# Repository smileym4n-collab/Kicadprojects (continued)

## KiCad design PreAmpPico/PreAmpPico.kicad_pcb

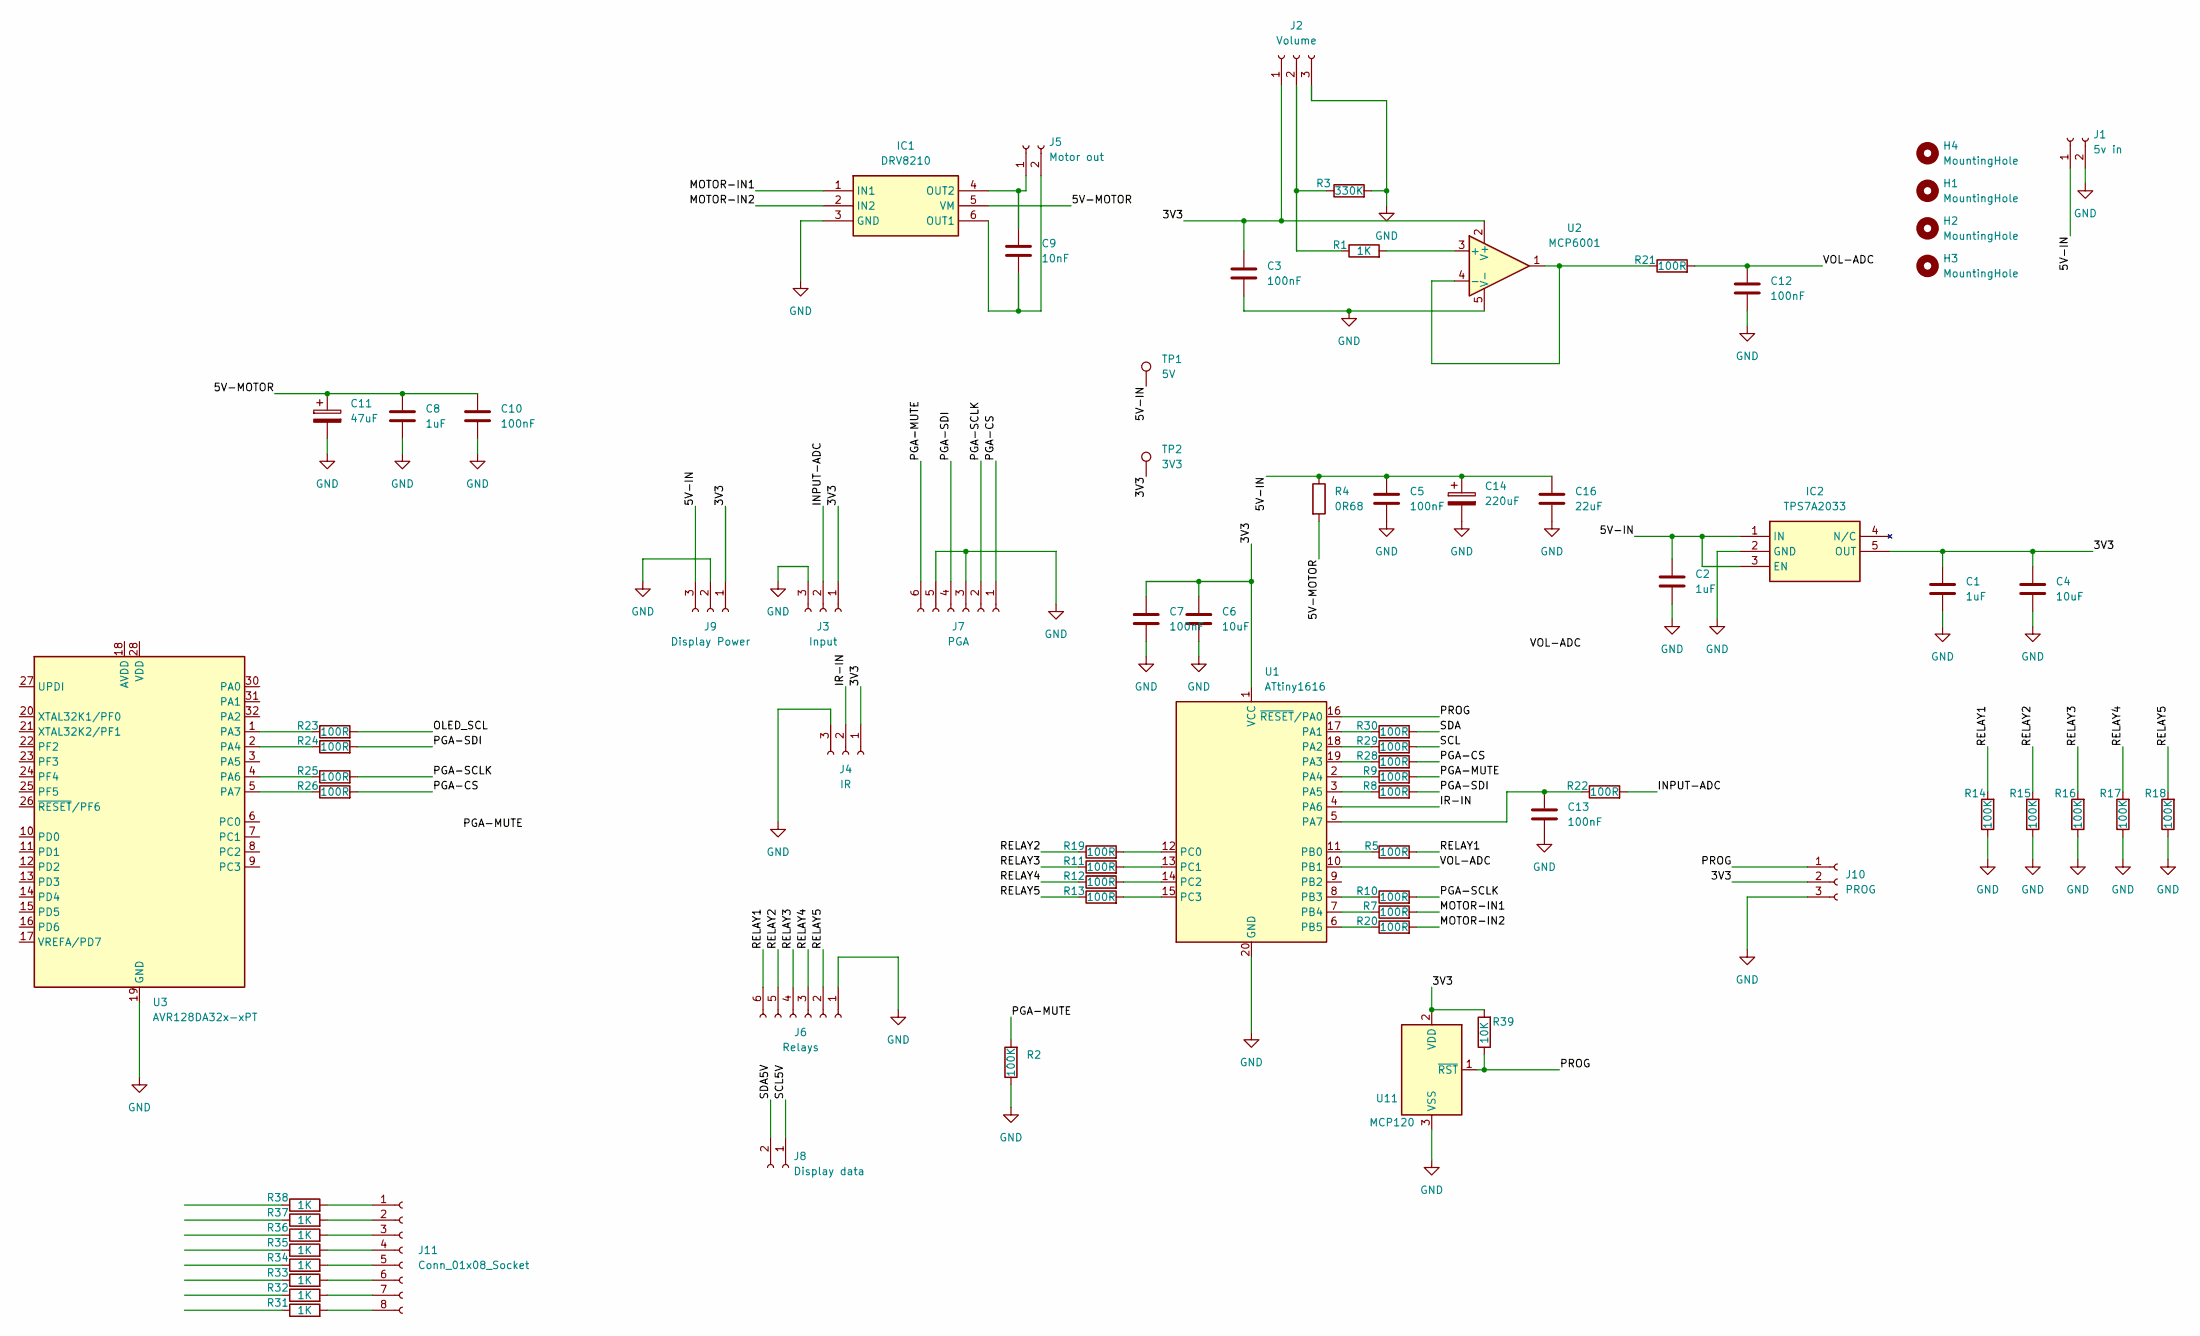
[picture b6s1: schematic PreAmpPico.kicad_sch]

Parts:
C1, C2, C8: 1uF; C_1206_3216Metric_Pad1.33x1.80mm_HandSolder
C3, C5, C7, C10, C12, C13: 100nF; C_1206_3216Metric_Pad1.33x1.80mm_HandSolder
C4, C6: 10uF; C_1206_3216Metric_Pad1.33x1.80mm_HandSolder
C9: 10nF; C_0805_2012Metric_Pad1.18x1.45mm_HandSolder
C11: 47uF; CP_Radial_D6.3mm_P2.50mm
C14: 220uF; CP_Radial_D6.3mm_P2.50mm
C16: 22uF; C_1206_3216Metric_Pad1.33x1.80mm_HandSolder
H1, H2, H3, H4: MountingHole; MountingHole_4mm
IC1: DRV8210; Mouser Part Number 595-DRV8210DRLR
IC2: TPS7A2033; SOT95P280X145-5N; Mouser Part Number 595-TPS7A2033PDBVR
J1: 5v in; JST_XH_B2B-XH-A_1x02_P2.50mm_Vertical
J2: Volume; JST_XH_B3B-XH-A_1x03_P2.50mm_Vertical
J3: Input; JST_XH_B3B-XH-A_1x03_P2.50mm_Vertical
J4: IR; JST_XH_B3B-XH-A_1x03_P2.50mm_Vertical
J5: Motor out; JST_XA_B02B-XASK-1_1x02_P2.50mm_Vertical
J6: Relays; JST_XH_B6B-XH-A_1x06_P2.50mm_Vertical
J7: PGA; JST_XH_B6B-XH-A_1x06_P2.50mm_Vertical
J8: Display data; JST_XA_B02B-XASK-1_1x02_P2.50mm_Vertical
J9: Display Power; JST_XH_B3B-XH-A_1x03_P2.50mm_Vertical
J10: PROG; PinSocket_1x03_P2.54mm_Vertical
J11: Conn_01x08_Socket; PinHeader_1x08_P2.54mm_Vertical
R1, R31, R32, R33, R34, R35, R36, R37, R38: 1K; R_0805_2012Metric_Pad1.20x1.40mm_HandSolder
R2, R14, R15, R16, R17, R18: 100K; R_0805_2012Metric_Pad1.20x1.40mm_HandSolder
R3: 330K; R_0805_2012Metric_Pad1.20x1.40mm_HandSolder
R4: 0R68; R_1206_3216Metric_Pad1.30x1.75mm_HandSolder
R5, R7, R8, R9, R10, R11, R12, R13, R19, R20, R21, R22, R23, R24, R25, R26, R28, R29, R30: 100R; R_0805_2012Metric_Pad1.20x1.40mm_HandSolder
R39: 10K; R_0805_2012Metric_Pad1.20x1.40mm_HandSolder
TP1: 5V; TestPoint_Pad_2.0x2.0mm
TP2: 3V3; TestPoint_Pad_2.0x2.0mm
U1: ATtiny1616; SSOP-20_5.3x7.2mm_P0.65mm
U2: MCP6001; SOT-23-5
U3: AVR128DA32x-xPT; TQFP-32_7x7mm_P0.8mm
U11: MCP120; SOT-23

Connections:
/3V3: C1.1, C3.1, C4.1, C6.1, C7.1, IC2.5 (OUT), J2.1, J3.1, J4.1, J9.1, J10.2, R39.2, TP2.1 (1_1), U1.1 (VCC), U2.2 (V+), U11.2 (VDD)
/5V-IN: C2.1, C5.1, C14.1, C16.1, IC2.1 (IN), IC2.3 (EN), J1.1, J9.3, R4.1, TP1.1 (1_1)
/5V-MOTOR: C8.1, C10.1, C11.1, IC1.5 (VM), R4.2
/INPUT-ADC: J3.2, R22.2
/IR-IN: J4.2, U1.4 (PA6)
/MOTOR-IN1: IC1.1 (IN1), R7.2
/MOTOR-IN2: IC1.2 (IN2), R20.2
/PGA-CS: J7.1, R26.2, R28.2
/PGA-MUTE: J7.6, R2.2, R9.2
/PGA-SCLK: J7.2, R10.2, R25.2
/PGA-SDI: J7.4, R8.2, R24.2
/PROG: J10.1, R39.1, U1.16 (~RESET/PA0), U11.1 (~RST)
/RELAY1: J6.6, R5.2, R14.2
/RELAY2: J6.5, R15.2, R19.1
/RELAY3: J6.4, R11.1, R16.2
/RELAY4: J6.3, R12.1, R17.2
/RELAY5: J6.2, R13.1, R18.2
/SCL: R29.2
/SCL5V: J8.1
/SDA: R30.2
/SDA5V: J8.2
/VOL-ADC: C12.1, R21.2, U1.10 (PB1)
unnamed: C9.2, IC1.6 (OUT1), J5.2
unnamed: C9.1, IC1.4 (OUT2), J5.1
unnamed: J2.2, R1.1, R3.1
unnamed: J11.1, R38.2
unnamed: J11.2, R37.2
unnamed: J11.3, R36.2
unnamed: J11.4, R35.2
unnamed: J11.5, R34.2
unnamed: J11.6, R33.2
unnamed: J11.7, R32.2
unnamed: J11.8, R31.2
unnamed: R23.1, U3.1 (PA3)
unnamed: R24.1, U3.2 (PA4)
unnamed: R25.1, U3.4 (PA6)
unnamed: R26.1, U3.5 (PA7)
unnamed: R30.1, U1.17 (PA1)
unnamed: R29.1, U1.18 (PA2)
unnamed: R28.1, U1.19 (PA3)
unnamed: R9.1, U1.2 (PA4)
unnamed: R8.1, U1.3 (PA5)
unnamed: C13.1, R22.1, U1.5 (PA7)
unnamed: R5.1, U1.11 (PB0)
unnamed: R10.1, U1.8 (PB3)
unnamed: R7.1, U1.7 (PB4)
unnamed: R20.1, U1.6 (PB5)
unnamed: R19.2, U1.12 (PC0)
unnamed: R11.2, U1.13 (PC1)
unnamed: R12.2, U1.14 (PC2)
unnamed: R13.2, U1.15 (PC3)
unnamed: R1.2, U2.3 (+)
unnamed: R21.1, U2.1, U2.4 (-)

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
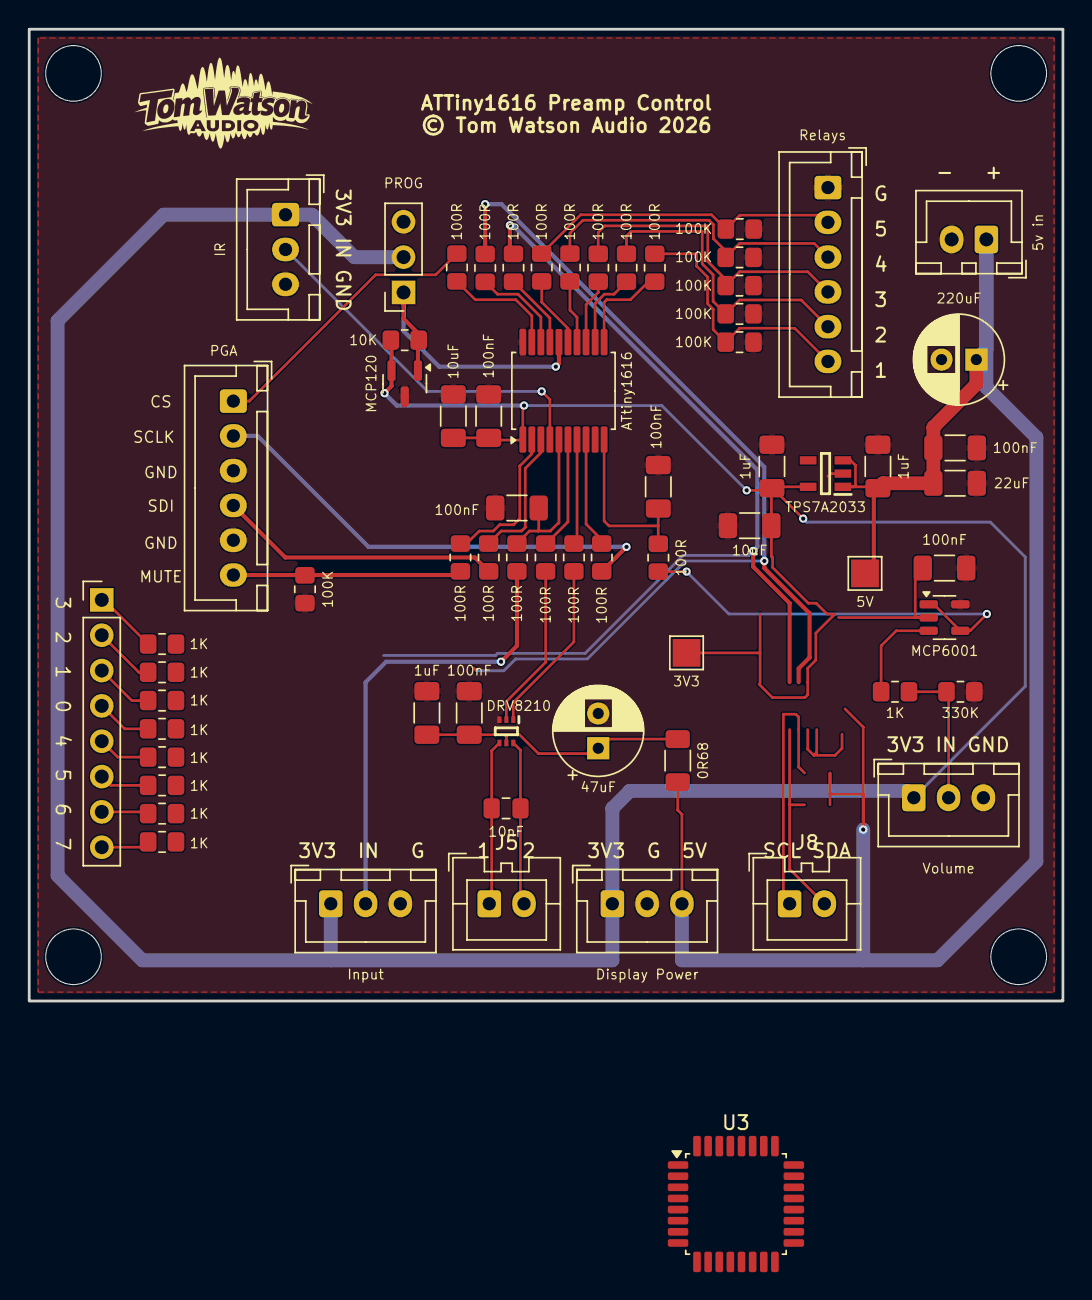
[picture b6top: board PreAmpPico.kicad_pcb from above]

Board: 2 copper layers, 74.3 x 69.9 mm, 71 parts (0 on the bottom side), 47 nets.

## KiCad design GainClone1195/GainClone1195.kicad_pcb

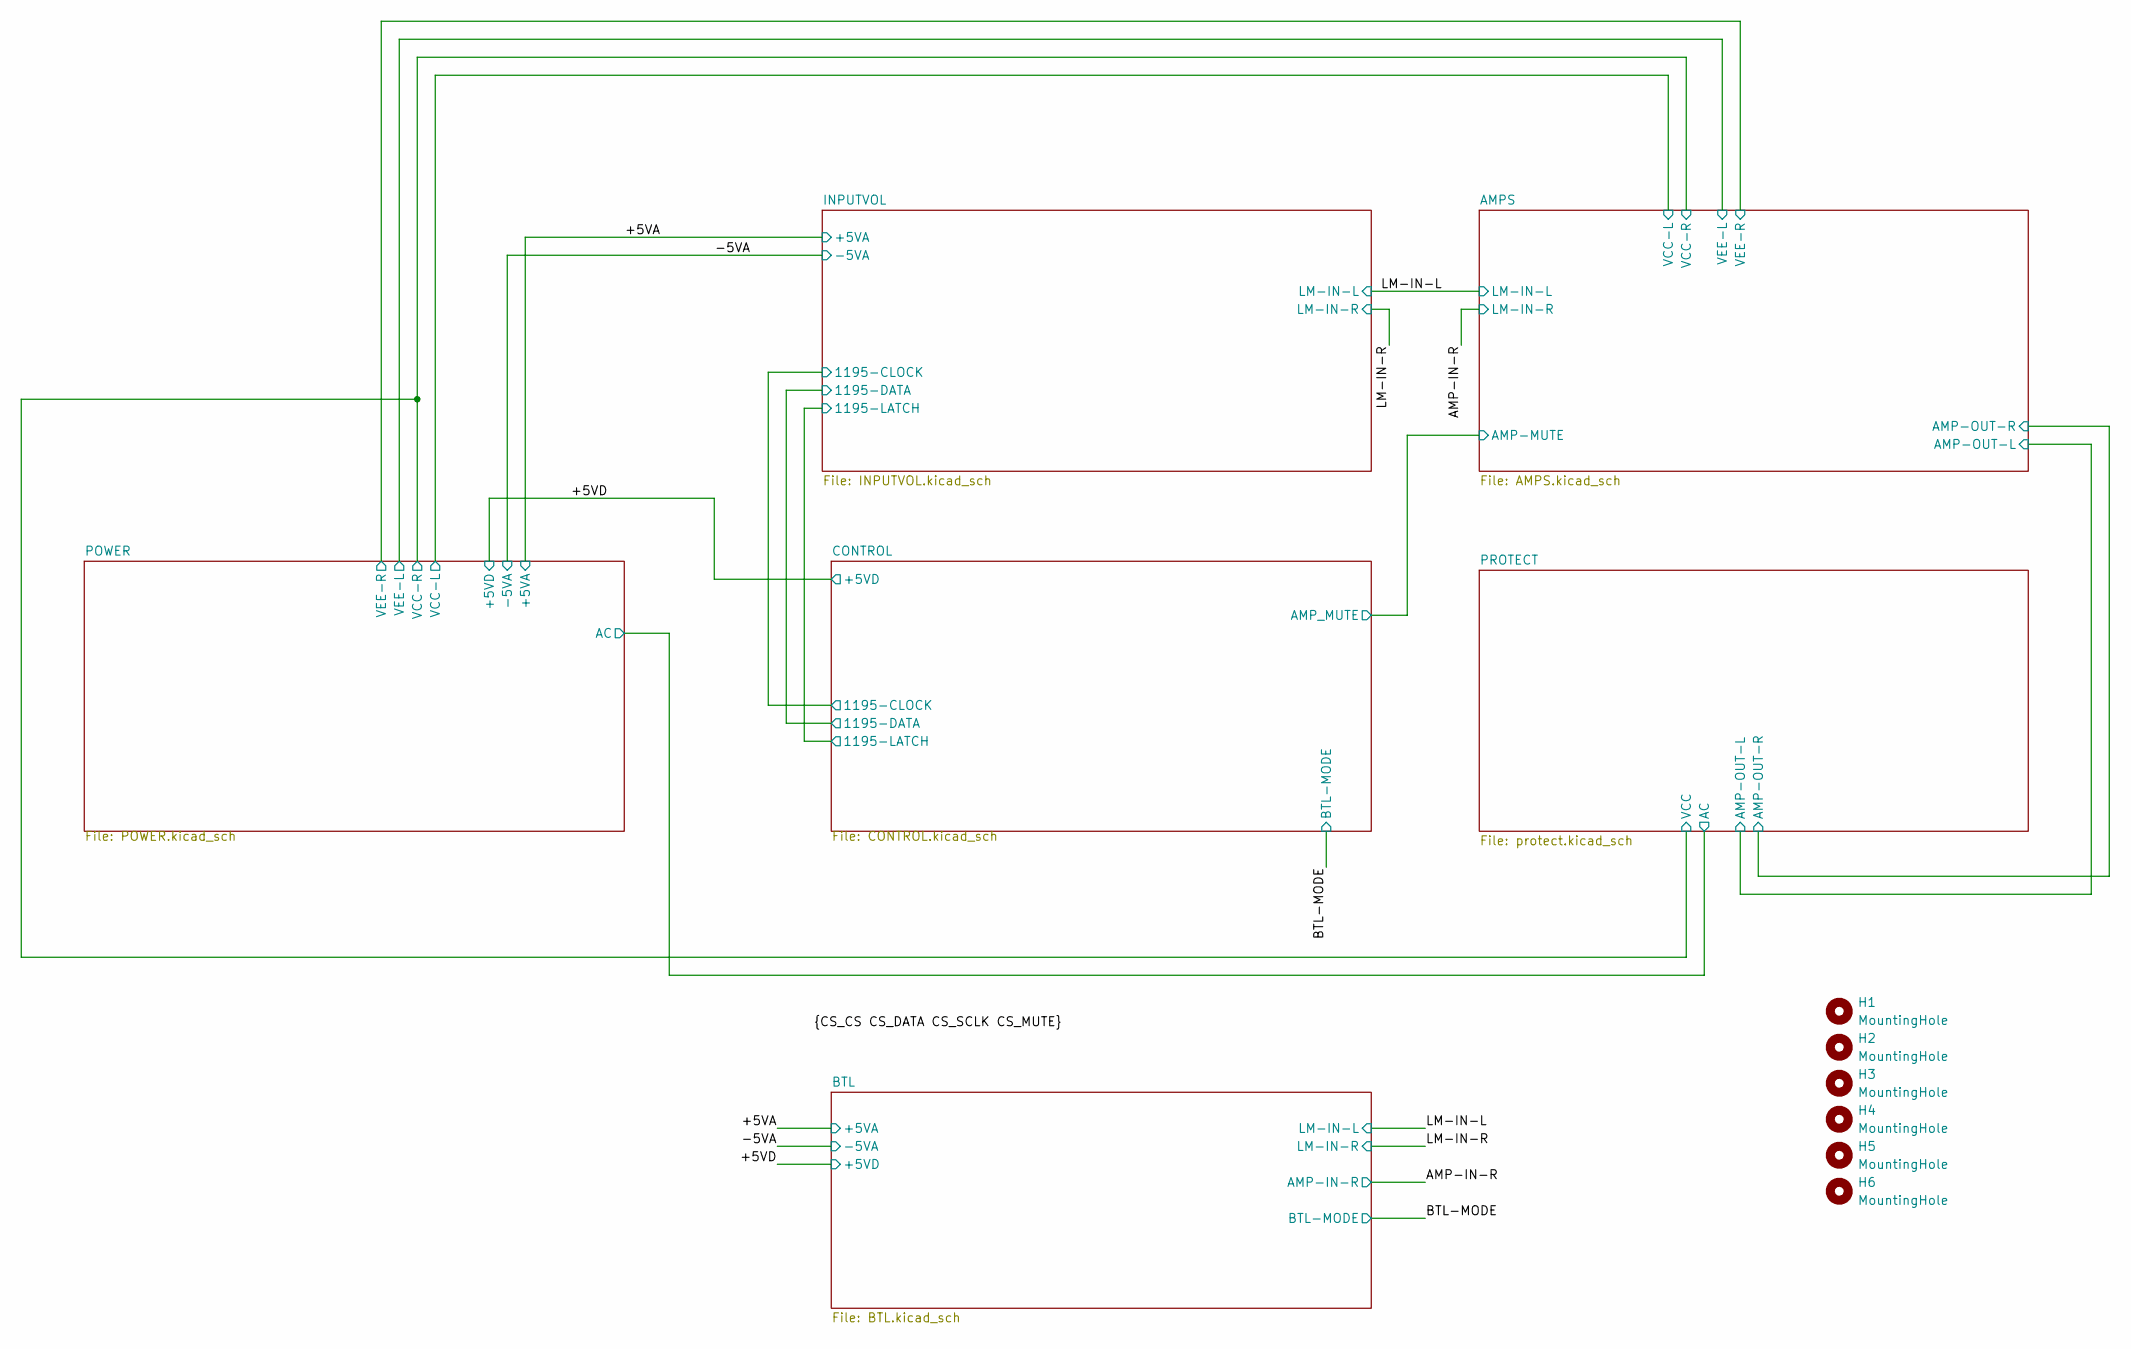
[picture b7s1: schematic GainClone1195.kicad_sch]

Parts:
H1, H2, H3, H4, H5, H6: MountingHole; MountingHole_3.2mm_M3

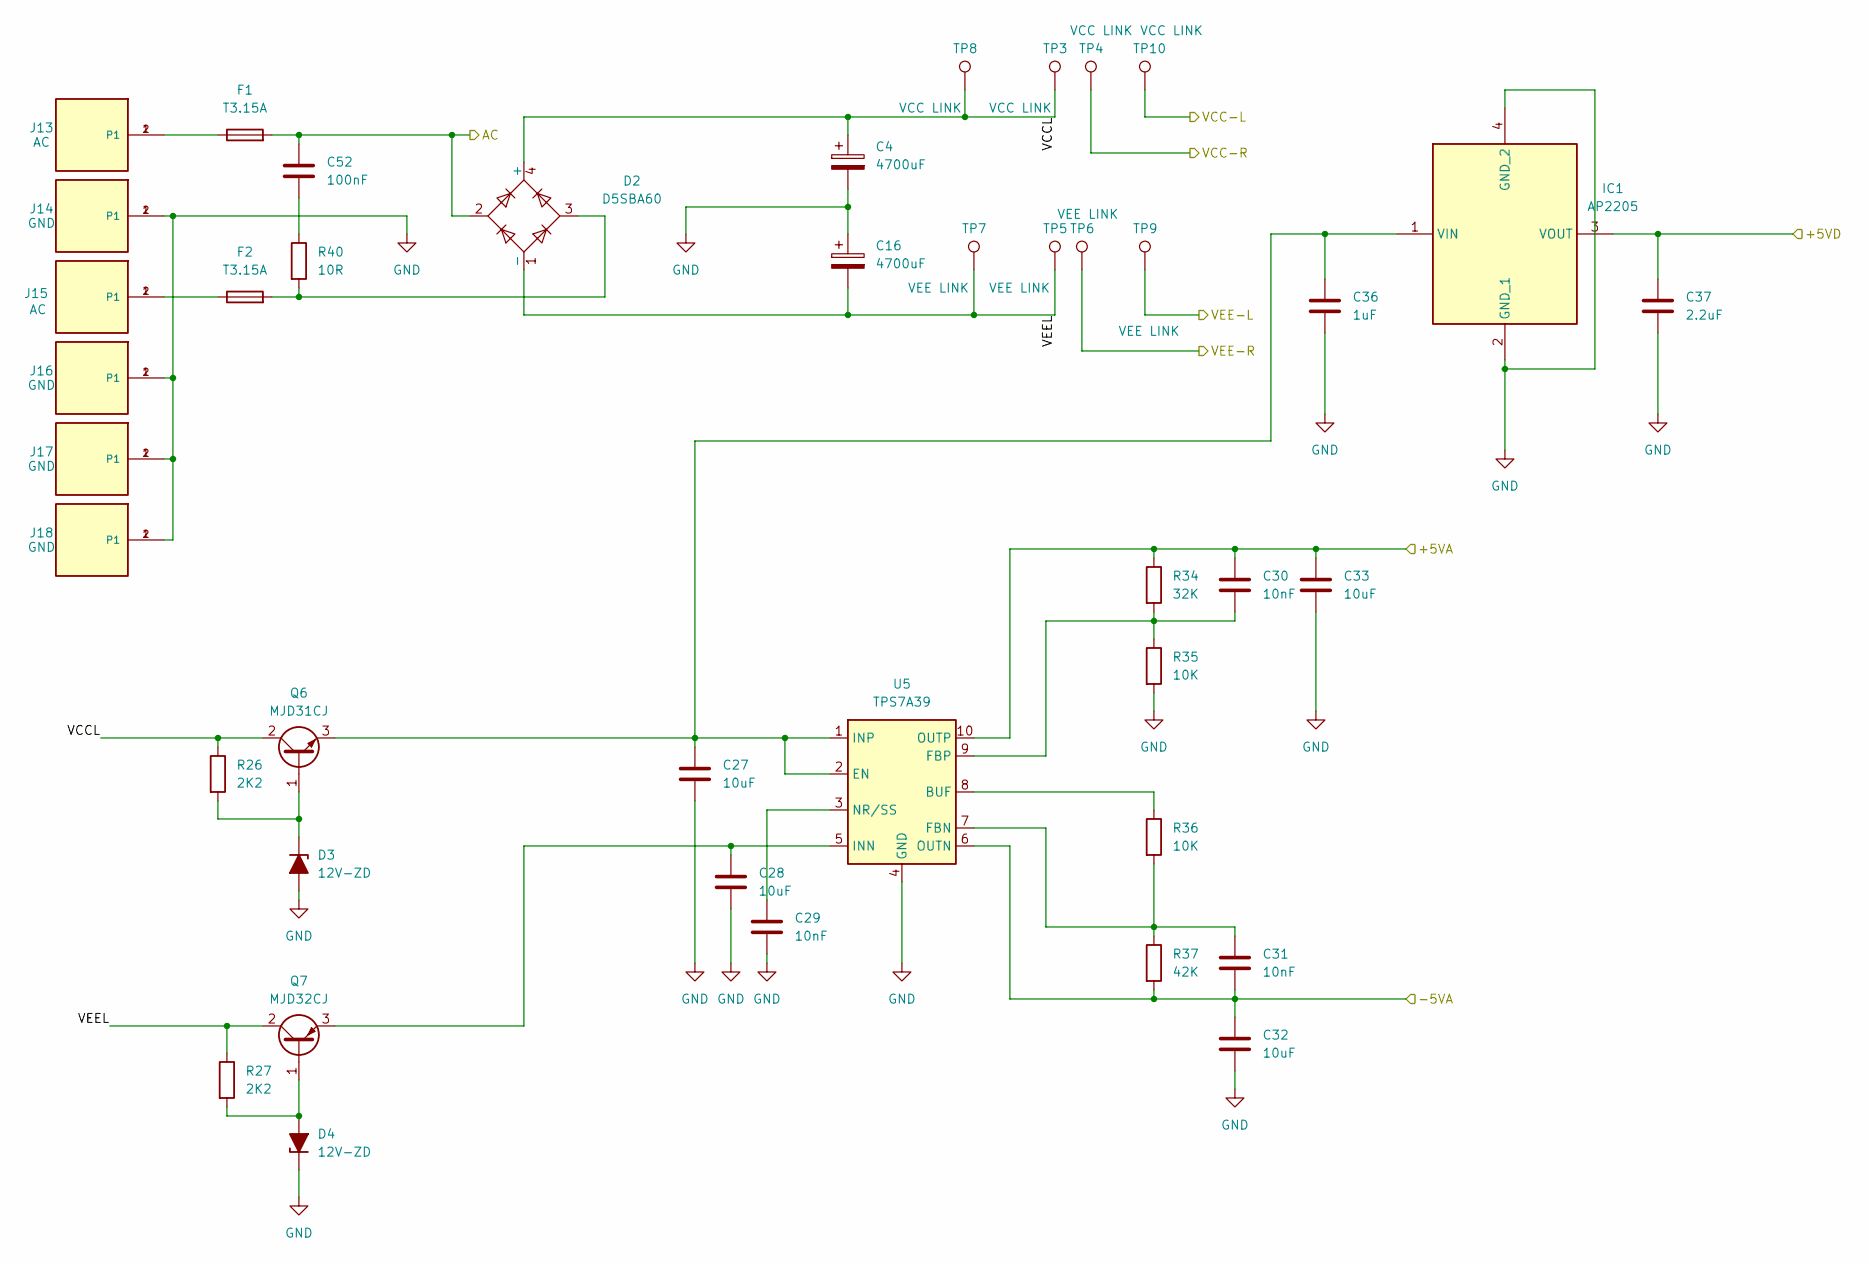
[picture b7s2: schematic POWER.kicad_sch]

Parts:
C4, C16: 4700uF; CP_Radial_D30.0mm_P10.00mm_SnapIn
C27, C28, C32, C33: 10uF; C_1206_3216Metric_Pad1.33x1.80mm_HandSolder
C29, C30, C31: 10nF; C_0805_2012Metric_Pad1.18x1.45mm_HandSolder
C36: 1uF; C_1206_3216Metric_Pad1.33x1.80mm_HandSolder
C37: 2.2uF; C_0805_2012Metric_Pad1.18x1.45mm_HandSolder
C52: 100nF; C_Rect_L18.0mm_W5.0mm_P15.00mm_FKS3_FKP3
D2: D5SBA60; Diode_Bridge_32.0x5.6x17.0mm_P10.0mm_P7.5mm
D3, D4: 12V-ZD; D_DO-201AD_P12.70mm_Horizontal
F1, F2: T3.15A; Fuse_Littelfuse_395Series
IC1: AP2205; SOT-89-3; Mouser Part Number 621-AP2205-50YR-13
J13, J15: AC; TE_62409-1; PART_DESCRIPTION CONN QC TAB 0.250 SOLDER
J14, J16, J17, J18: GND; TE_62409-1; PART_DESCRIPTION CONN QC TAB 0.250 SOLDER
Q6: MJD31CJ; TO-252-3_TabPin2
Q7: MJD32CJ; TO-252-3_TabPin2
R26, R27: 2K2; R_Axial_DIN0207_L6.3mm_D2.5mm_P10.16mm_Horizontal
R34: 32K; R_0805_2012Metric_Pad1.20x1.40mm_HandSolder
R35, R36: 10K; R_0805_2012Metric_Pad1.20x1.40mm_HandSolder
R37: 42K; R_0805_2012Metric_Pad1.20x1.40mm_HandSolder
R40: 10R; R_Axial_DIN0617_L17.0mm_D6.0mm_P20.32mm_Horizontal
TP3, TP4, TP8, TP10: VCC LINK; TestPoint_THTPad_D4.0mm_Drill2.0mm
TP5, TP6, TP7, TP9: VEE LINK; TestPoint_THTPad_D4.0mm_Drill2.0mm
U5: TPS7A39; Texas_S-PVSON-N10_ThermalVias

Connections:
/+5VA: C30.1, C33.1, R34.1, U5.10 (OUTP); also elsewhere on the board
/+5VD: C37.1, IC1.3 (VOUT); also elsewhere on the board
/-5VA: C31.2, C32.1, R37.2, U5.6 (OUTN); also elsewhere on the board
/AMPS/VCC-L: TP10.1 (1_1); also elsewhere on the board
/AMPS/VCC-R: TP4.1 (1_1); also elsewhere on the board
/AMPS/VEE-L: TP9.1 (1_1); also elsewhere on the board
/AMPS/VEE-R: TP6.1 (1_1); also elsewhere on the board
/POWER/AC: C52.1, D2.2, F1.2; also elsewhere on the board
/POWER/VCCL: C4.1, D2.4 (+), Q6.2 (C), R26.1, TP3.1 (1_1), TP8.1 (1_1)
/POWER/VEEL: C16.2, D2.1 (-), Q7.2 (C), R27.1, TP5.1 (1_1), TP7.1 (1_1)
GND: C4.2, C16.1, C27.2, C28.2, C29.2, C32.2, C33.2, C36.2, C37.2, D3.2 (A), D4.1 (K), IC1.2 (GND_1), IC1.4 (GND_2), J14.1, J14.2 (P1), J16.1, J16.2 (P1), J17.1, J17.2 (P1), J18.1, J18.2 (P1), R35.2, U5.4 (GND), U5.11 (GND); also elsewhere on the board
unnamed: C52.2, R40.1
unnamed: D2.3, F2.2, R40.2
unnamed: D3.1 (K), Q6.1 (B), R26.2
unnamed: D4.2 (A), Q7.1 (B), R27.2
unnamed: F1.1, J13.1, J13.2 (P1)
unnamed: F2.1, J15.1, J15.2 (P1)
unnamed: C27.1, C36.1, IC1.1 (VIN), Q6.3 (E), U5.1 (INP), U5.2 (EN)
unnamed: C28.1, Q7.3 (E), U5.5 (INN)
unnamed: R36.1, U5.8 (BUF)
unnamed: C31.1, R36.2, R37.1, U5.7 (FBN)
unnamed: C30.2, R34.2, R35.1, U5.9 (FBP)
unnamed: C29.1, U5.3 (NR/SS)

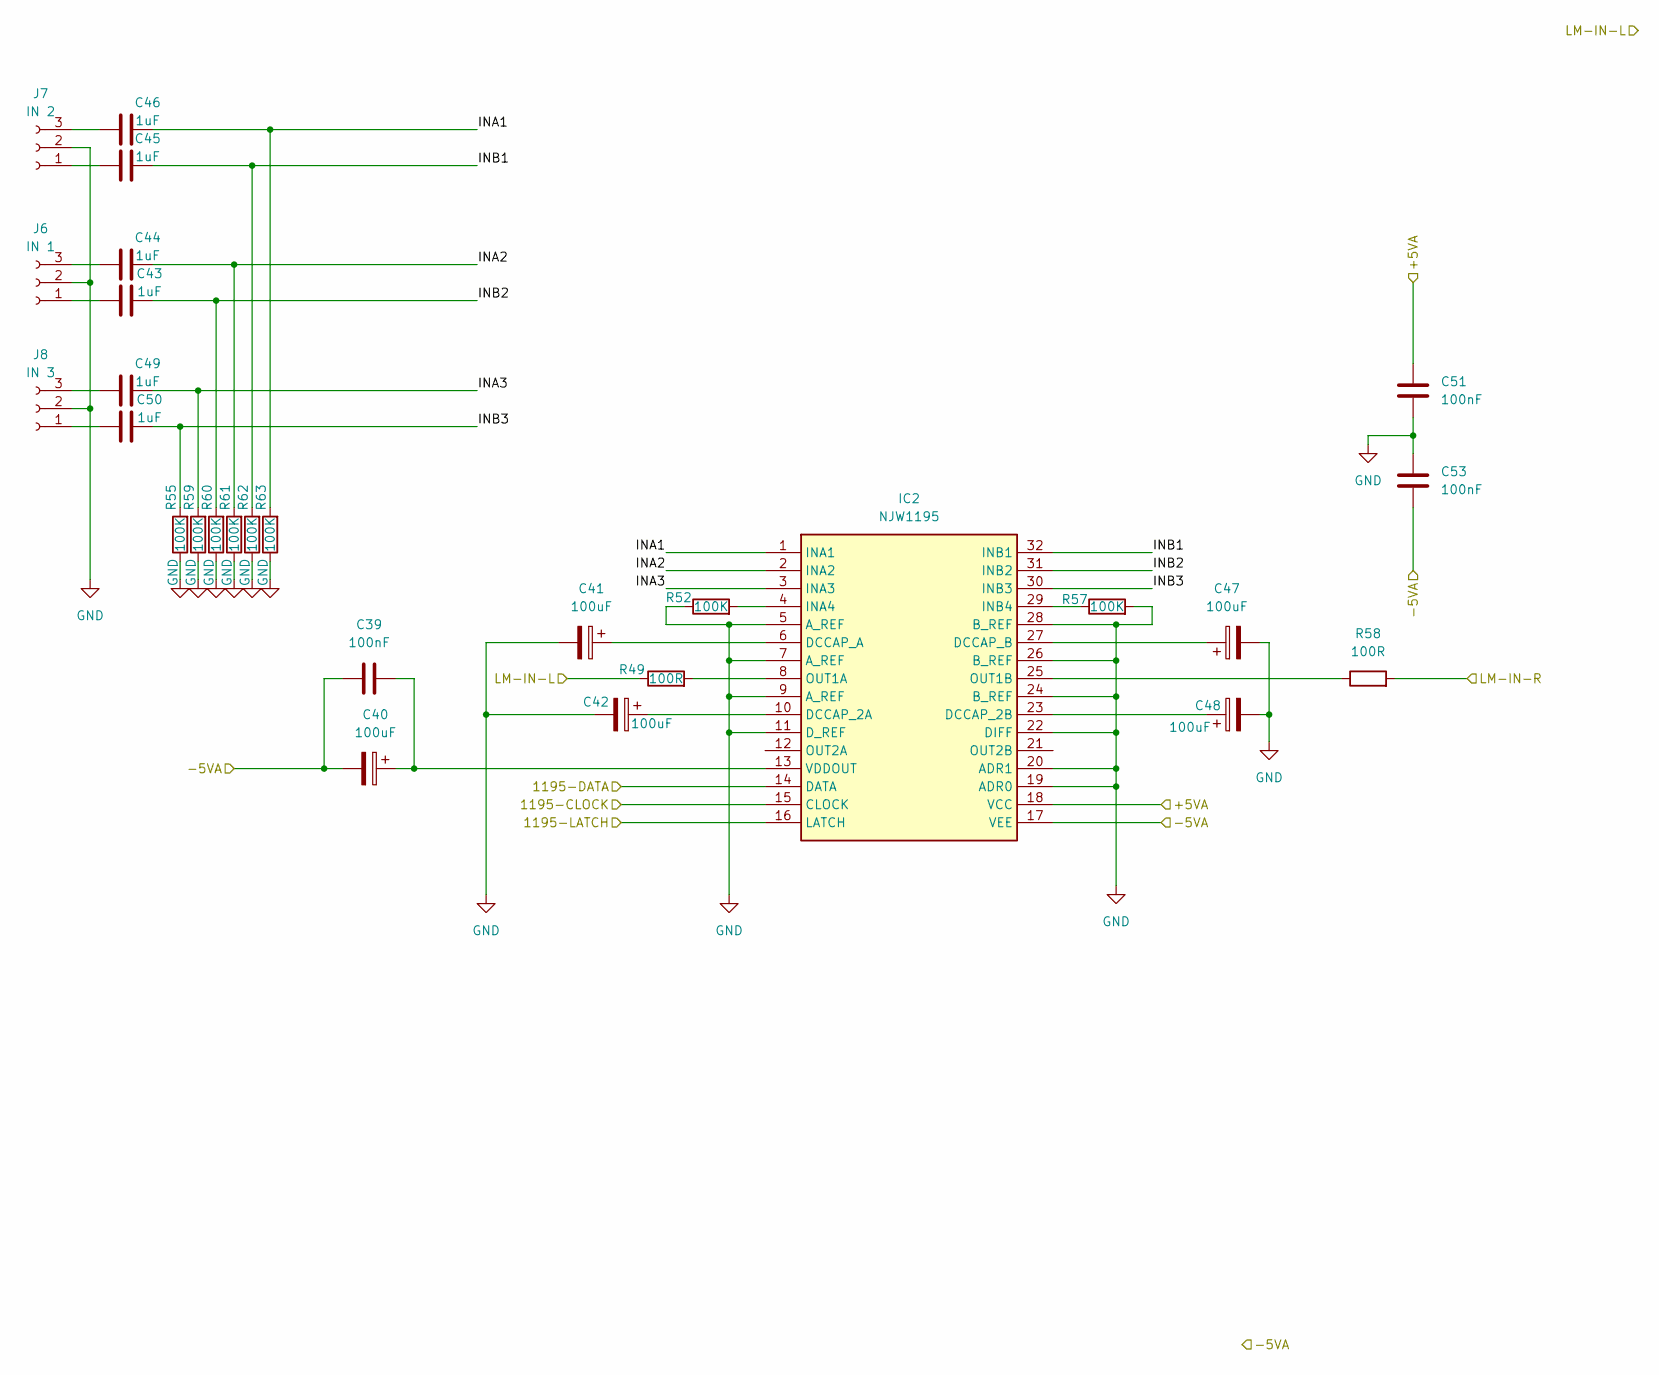
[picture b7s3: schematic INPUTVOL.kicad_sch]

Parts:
C39, C51, C53: 100nF; C_0603_1608Metric_Pad1.08x0.95mm_HandSolder
C40, C41, C42, C47, C48: 100uF; CP_Radial_D6.3mm_P2.50mm
C43, C44, C45, C46, C49, C50: 1uF; C_Rect_L7.2mm_W5.5mm_P5.00mm_FKS2_FKP2_MKS2_MKP2
IC2: NJW1195; SOP65P760X145-32N; Manufacturer_Part_Number NJW1194V-TE1; Mouser Part Number 513-NJW1194V-TE1
J6: IN 1; JST_XH_B3B-XH-A_1x03_P2.50mm_Vertical
J7: IN 2; JST_XH_B3B-XH-A_1x03_P2.50mm_Vertical
J8: IN 3; JST_XH_B3B-XH-A_1x03_P2.50mm_Vertical
R49, R58: 100R; R_0805_2012Metric_Pad1.20x1.40mm_HandSolder
R52, R55, R57, R59, R60, R61, R62, R63: 100K; R_0805_2012Metric_Pad1.20x1.40mm_HandSolder

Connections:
/+5VA: C51.1, IC2.18 (VCC); also elsewhere on the board
/-5VA: C39.1, C40.2, C53.2, IC2.17 (VEE); also elsewhere on the board
/CONTROL/1195-CLOCK: IC2.15 (CLOCK); also elsewhere on the board
/CONTROL/1195-DATA: IC2.14 (DATA); also elsewhere on the board
/CONTROL/1195-LATCH: IC2.16 (LATCH); also elsewhere on the board
/INPUTVOL/INA1: C46.2, IC2.1 (INA1), R63.2
/INPUTVOL/INA2: C44.2, IC2.2 (INA2), R61.2
/INPUTVOL/INA3: C49.2, IC2.3 (INA3), R59.2
/INPUTVOL/INB1: C45.2, IC2.32 (INB1), R62.2
/INPUTVOL/INB2: C43.2, IC2.31 (INB2), R60.2
/INPUTVOL/INB3: C50.2, IC2.30 (INB3), R55.2
/LM-IN-L: R49.1; also elsewhere on the board
/LM-IN-R: R58.2; also elsewhere on the board
GND: C41.2, C42.2, C47.2, C48.2, C51.2, C53.1, IC2.5 (A_REF), IC2.7 (A_REF), IC2.9 (A_REF), IC2.11 (D_REF), IC2.19 (ADR0), IC2.20 (ADR1), IC2.22 (DIFF), IC2.24 (B_REF), IC2.26 (B_REF), IC2.28 (B_REF), J6.2, J7.2, J8.2, R52.1, R55.1, R57.2, R59.1, R60.1, R61.1, R62.1, R63.1; also elsewhere on the board
unnamed: C42.1, IC2.10 (DCCAP_2A)
unnamed: C48.1, IC2.23 (DCCAP_2B)
unnamed: C41.1, IC2.6 (DCCAP_A)
unnamed: C47.1, IC2.27 (DCCAP_B)
unnamed: IC2.4 (INA4), R52.2
unnamed: IC2.29 (INB4), R57.1
unnamed: IC2.8 (OUT1A), R49.2
unnamed: IC2.25 (OUT1B), R58.1
unnamed: C39.2, C40.1, IC2.13 (VDDOUT)
unnamed: C43.1, J6.1
unnamed: C44.1, J6.3
unnamed: C45.1, J7.1
unnamed: C46.1, J7.3
unnamed: C50.1, J8.1
unnamed: C49.1, J8.3

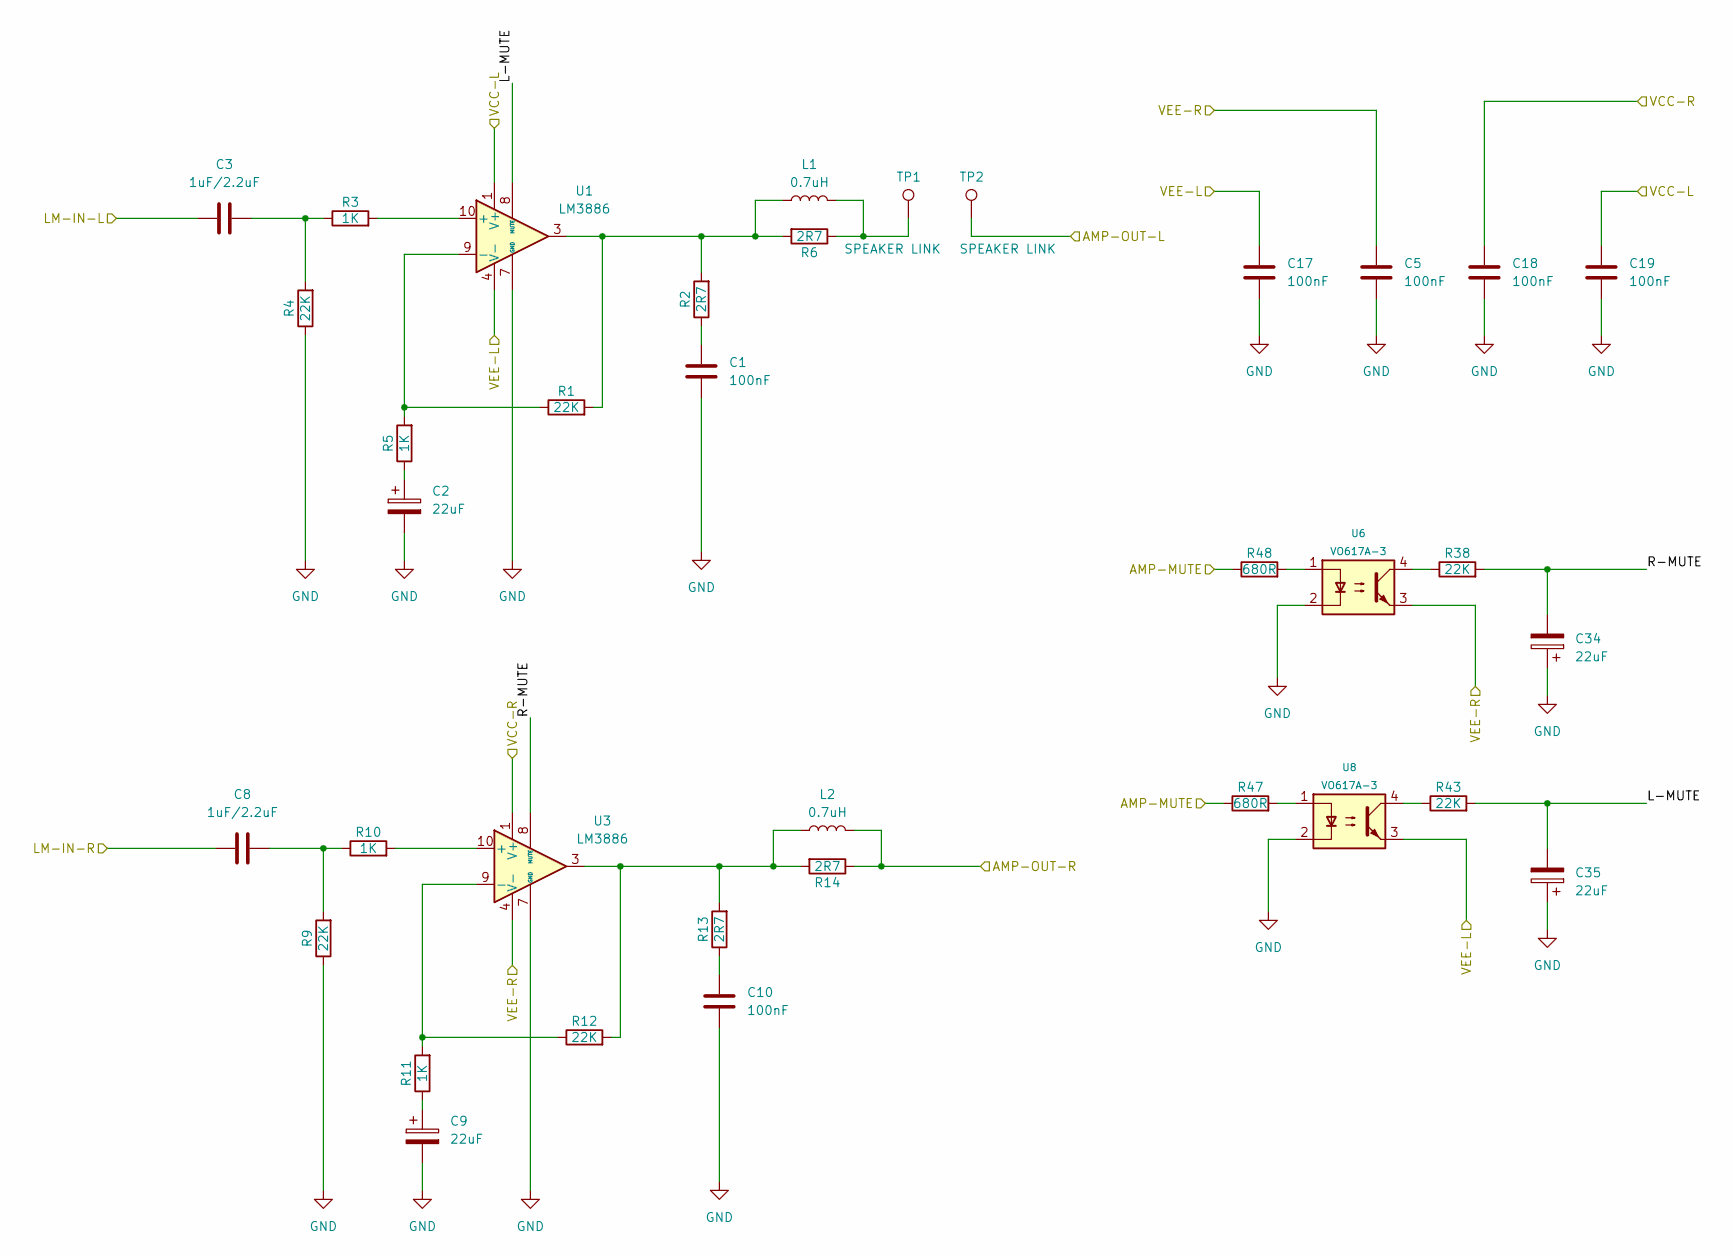
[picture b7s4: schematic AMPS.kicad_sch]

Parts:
C1, C10: 100nF; C_Rect_L7.2mm_W2.5mm_P5.00mm_FKS2_FKP2_MKS2_MKP2
C2, C9, C34, C35: 22uF; CP_Radial_D5.0mm_P2.50mm
C3, C8: 1uF/2.2uF; C_Rect_L7.2mm_W7.2mm_P5.00mm_FKS2_FKP2_MKS2_MKP2
C5, C17, C18, C19: 100nF; C_1206_3216Metric_Pad1.33x1.80mm_HandSolder
L1, L2: 0.7uH
R1, R4, R9, R12, R38, R43: 22K; R_0805_2012Metric_Pad1.20x1.40mm_HandSolder
R2, R6, R13, R14: 2R7; R_Axial_DIN0309_L9.0mm_D3.2mm_P12.70mm_Horizontal
R3, R5, R10, R11: 1K; R_0805_2012Metric_Pad1.20x1.40mm_HandSolder
R47, R48: 680R; R_0805_2012Metric_Pad1.20x1.40mm_HandSolder
TP1, TP2: SPEAKER LINK; TestPoint_THTPad_D4.0mm_Drill2.0mm
U1, U3: LM3886; TO-220-11_P3.4x5.08mm_StaggerOdd_Lead4.58mm_Vertical
U6, U8: VO617A-3; DIP-4_W7.62mm

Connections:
/AMP-IN-R: C8.1; also elsewhere on the board
/AMPS/AMP-MUTE: R47.1, R48.1; also elsewhere on the board
/AMPS/AMP-OUT-L: TP2.1 (1_1); also elsewhere on the board
/AMPS/AMP-OUT-R: L2.2, R14.1; also elsewhere on the board
/AMPS/L-MUTE: C35.2, R43.2, U1.8 (MUTE)
/AMPS/R-MUTE: C34.2, R38.2, U3.8 (MUTE)
/AMPS/VCC-L: C19.1, U1.1 (V+), U1.5 (V+); also elsewhere on the board
/AMPS/VCC-R: C18.1, U3.1 (V+), U3.5 (V+); also elsewhere on the board
/AMPS/VEE-L: C17.1, U1.4 (V-), U8.3; also elsewhere on the board
/AMPS/VEE-R: C5.1, U3.4 (V-), U6.3; also elsewhere on the board
/LM-IN-L: C3.1; also elsewhere on the board
GND: C1.2, C2.2, C5.2, C9.2, C10.2, C17.2, C18.2, C19.2, C34.1, C35.1, R4.1, R9.1, U1.7 (GND), U3.7 (GND), U6.2, U8.2; also elsewhere on the board
unnamed: C1.1, R2.1
unnamed: C2.1, R5.1
unnamed: C3.2, R3.1, R4.2
unnamed: C8.2, R9.2, R10.1
unnamed: C9.1, R11.1
unnamed: C10.1, R13.1
unnamed: L1.1, R1.2, R2.2, R6.2, U1.3
unnamed: L1.2, R6.1, TP1.1 (1_1)
unnamed: L2.1, R12.2, R13.2, R14.2, U3.3
unnamed: R38.1, U6.4
unnamed: R43.1, U8.4
unnamed: R47.2, U8.1
unnamed: R48.2, U6.1
unnamed: R3.2, U1.10 (+)
unnamed: R1.1, R5.2, U1.9 (-)
unnamed: R10.2, U3.10 (+)
unnamed: R11.2, R12.1, U3.9 (-)

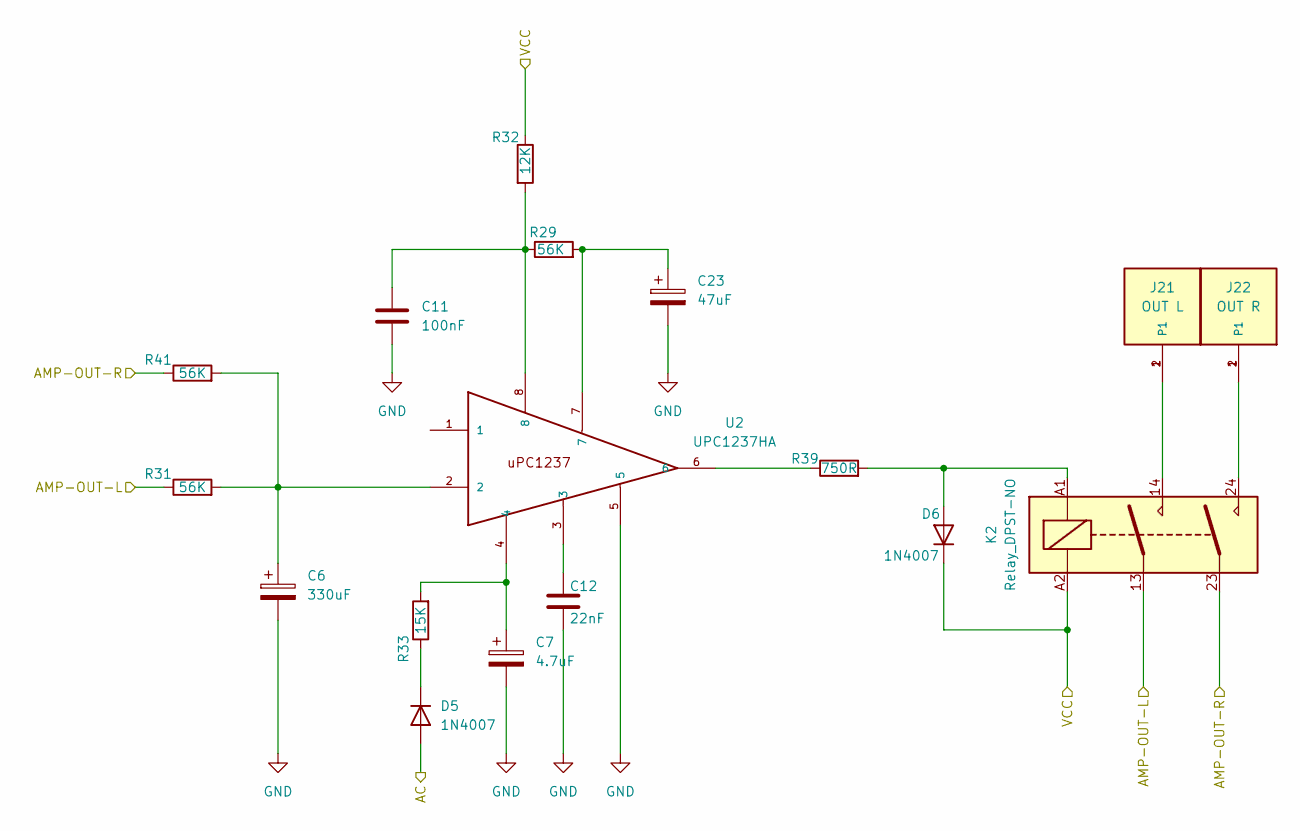
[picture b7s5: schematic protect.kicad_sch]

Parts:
C6: 330uF; CP_Radial_D8.0mm_P2.50mm
C7: 4.7uF; CP_Radial_D5.0mm_P2.50mm
C11: 100nF; C_0603_1608Metric_Pad1.08x0.95mm_HandSolder
C12: 22nF; C_Rect_L7.2mm_W2.5mm_P5.00mm
C23: 47uF; CP_Radial_D5.0mm_P2.50mm
D5, D6: 1N4007; D_DO-41_SOD81_P10.16mm_Horizontal
J21: OUT L; TE_62409-1; PART_DESCRIPTION CONN QC TAB 0.250 SOLDER
J22: OUT R; TE_62409-1; PART_DESCRIPTION CONN QC TAB 0.250 SOLDER
K2: Relay_DPST-NO; Relay_DPST_Omron_G2RL-2A
R29, R31, R41: 56K; R_1206_3216Metric_Pad1.30x1.75mm_HandSolder
R32: 12K; R_Axial_DIN0207_L6.3mm_D2.5mm_P10.16mm_Horizontal
R33: 15K; R_Axial_DIN0207_L6.3mm_D2.5mm_P10.16mm_Horizontal
R39: 750R; R_Axial_DIN0207_L6.3mm_D2.5mm_P10.16mm_Horizontal
U2: UPC1237HA; SIP-8_19x3mm_P2.54mm

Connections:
/AMPS/AMP-OUT-L: K2.13, R31.1; also elsewhere on the board
/AMPS/AMP-OUT-R: K2.23, R41.1; also elsewhere on the board
/AMPS/VCC-R: D6.1 (K), K2.A2, R32.1; also elsewhere on the board
/POWER/AC: D5.2 (A); also elsewhere on the board
GND: C6.2, C7.2, C11.2, C12.2, C23.2, U2.5; also elsewhere on the board
unnamed: C6.1, R31.2, R41.2, U2.2
unnamed: C7.1, R33.2, U2.4
unnamed: C11.1, R29.1, R32.2, U2.8
unnamed: C12.1, U2.3
unnamed: C23.1, R29.2, U2.7
unnamed: D5.1 (K), R33.1
unnamed: D6.2 (A), K2.A1, R39.2
unnamed: J21.1, J21.2 (P1), K2.14
unnamed: J22.1, J22.2 (P1), K2.24
unnamed: R39.1, U2.6
